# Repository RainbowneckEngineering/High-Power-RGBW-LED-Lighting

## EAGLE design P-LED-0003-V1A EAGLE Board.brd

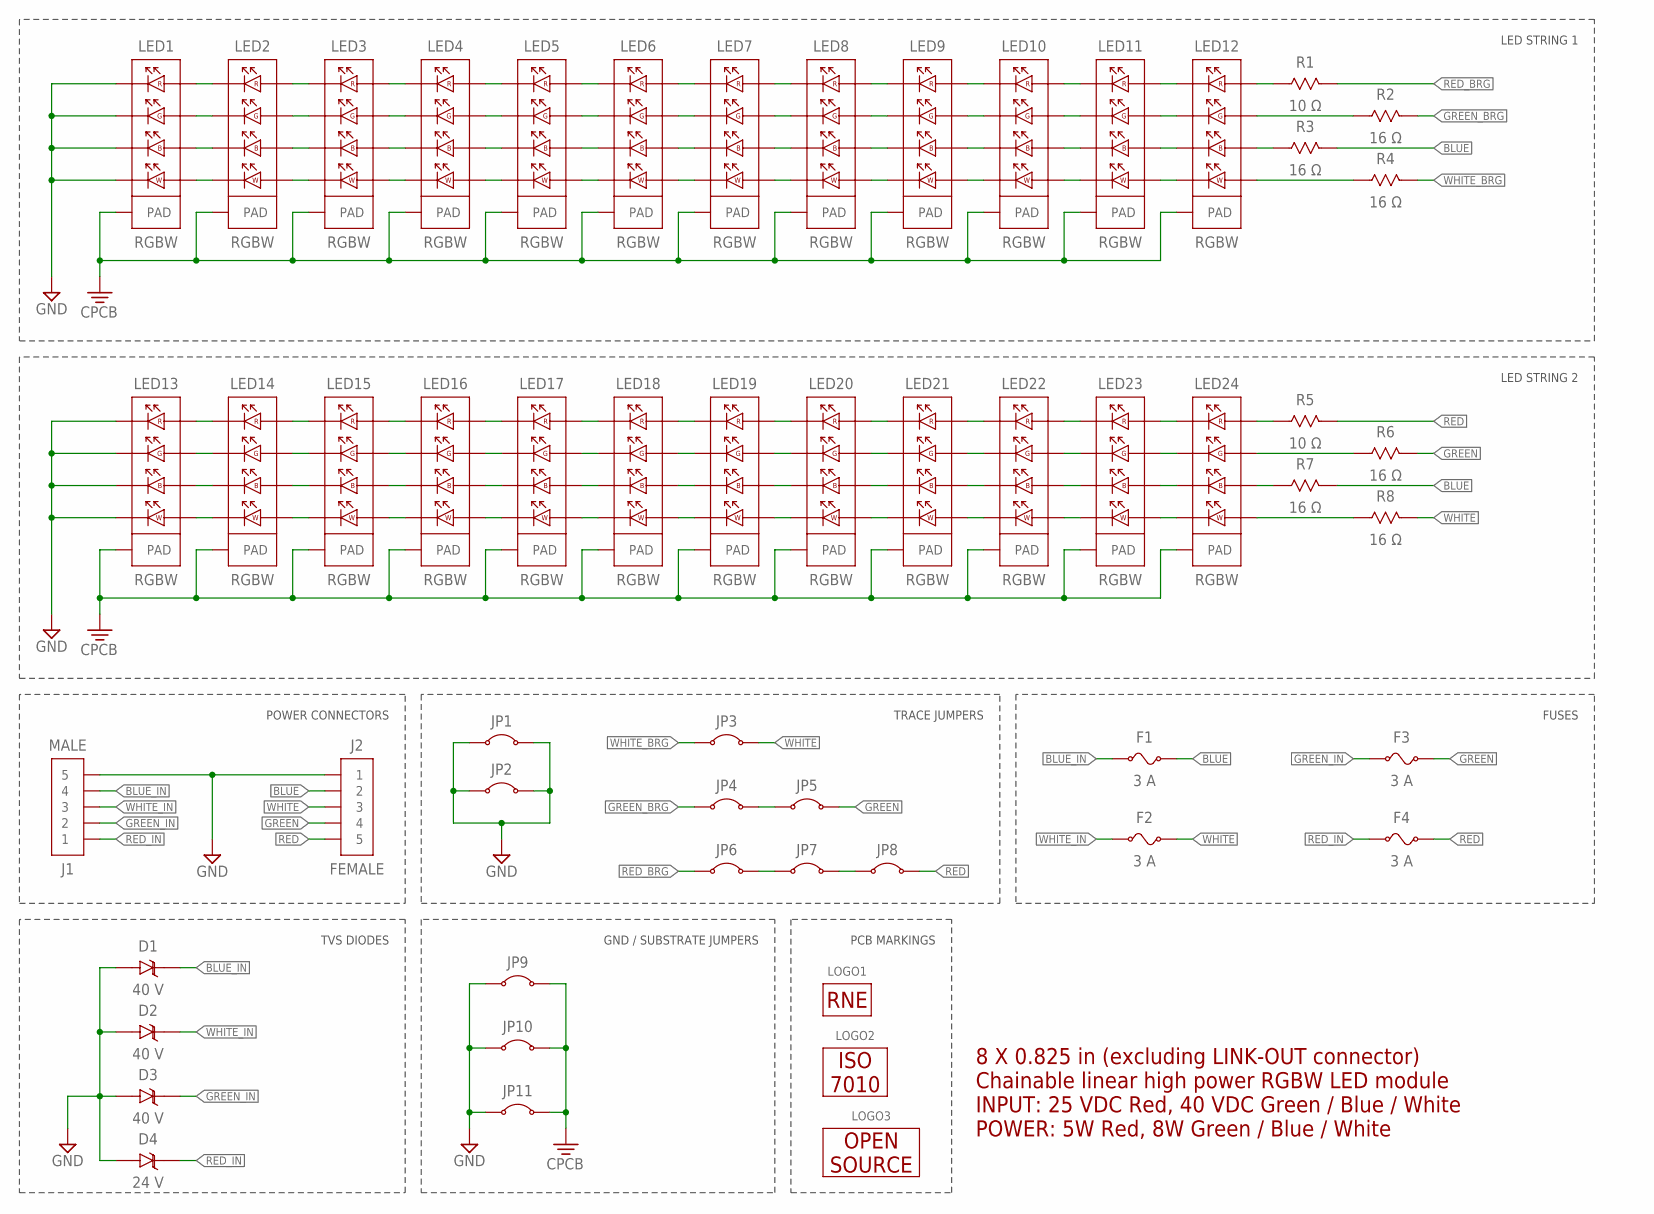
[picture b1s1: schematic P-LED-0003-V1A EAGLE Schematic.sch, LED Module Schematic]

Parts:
D1, D2, D3: 40 V; 0603_POLARIZED
D4: 24 V; 0603_POLARIZED
F1, F2, F3, F4: 3 A; 1206
J1: MALE; 5-PIN_1-ROW_MALE_SMD_HORIZONTAL
J2: FEMALE; 5-PIN_1-ROW_FEMALE_SMD_HORIZONTAL
JP1, JP2, JP3, JP4, JP5, JP6, JP7, JP8: JUMPERSMD_1206; 1206
JP9, JP10, JP11: DCH_JUMPERSMD_0603; 0603
LED1, LED2, LED3, LED4, LED5, LED6, LED7, LED8, LED9, LED10, LED11, LED12, LED13, LED14, LED15, LED16, LED17, LED18, LED19, LED20, LED21, LED22, LED23, LED24: RGBW; IN-P55QSTGRGBW
LOGO1: PROFILE_LOGO_RNE0.375"; RNE_PROFILE-LOGO_375
LOGO2: HOT_SURFACE_ISO0.375"_LABEL; ISO_HOT-SURFACE_375_LABEL
LOGO3: OPEN_SOURCE_OSHWA0.375"_LABEL; OSHWA_OPEN-SOURCE_375_LABEL
R1, R5: 10 Ω; 0603
R2, R3, R4, R6, R7, R8: 16 Ω; 0603

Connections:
B1_RESISTOR: LED12.BLUE_P, R3.1
B2_RESISTOR: LED24.BLUE_P, R7.1
BLUE: F1.2, J2.2, R3.2, R7.2
BLUE_IN: D1.K, F1.1, J1.4
B_12: LED1.BLUE_P, LED2.BLUE_N
B_23: LED2.BLUE_P, LED3.BLUE_N
B_34: LED3.BLUE_P, LED4.BLUE_N
B_45: LED4.BLUE_P, LED5.BLUE_N
B_56: LED5.BLUE_P, LED6.BLUE_N
B_67: LED6.BLUE_P, LED7.BLUE_N
B_78: LED7.BLUE_P, LED8.BLUE_N
B_89: LED8.BLUE_P, LED9.BLUE_N
B_910: LED9.BLUE_P, LED10.BLUE_N
B_1011: LED10.BLUE_P, LED11.BLUE_N
B_1112: LED11.BLUE_P, LED12.BLUE_N
B_1314: LED13.BLUE_P, LED14.BLUE_N
B_1415: LED14.BLUE_P, LED15.BLUE_N
B_1516: LED15.BLUE_P, LED16.BLUE_N
B_1617: LED16.BLUE_P, LED17.BLUE_N
B_1718: LED17.BLUE_P, LED18.BLUE_N
B_1819: LED18.BLUE_P, LED19.BLUE_N
B_1920: LED19.BLUE_P, LED20.BLUE_N
B_2021: LED20.BLUE_P, LED21.BLUE_N
B_2122: LED21.BLUE_P, LED22.BLUE_N
B_2223: LED22.BLUE_P, LED23.BLUE_N
B_2324: LED23.BLUE_P, LED24.BLUE_N
G1_RESISTOR: LED12.GREEN_P, R2.1
G2_RESISTOR: LED24.GREEN_P, R6.1
GREEN: F3.2, J2.4, JP5.2, R6.2
GREEN_BRG: JP4.1, R2.2
GREEN_BRG_2: JP4.2, JP5.1
GREEN_IN: D3.K, F3.1, J1.2
G_12: LED1.GREEN_P, LED2.GREEN_N
G_23: LED2.GREEN_P, LED3.GREEN_N
G_34: LED3.GREEN_P, LED4.GREEN_N
G_45: LED4.GREEN_P, LED5.GREEN_N
G_56: LED5.GREEN_P, LED6.GREEN_N
G_67: LED6.GREEN_P, LED7.GREEN_N
G_78: LED7.GREEN_P, LED8.GREEN_N
G_89: LED8.GREEN_P, LED9.GREEN_N
G_910: LED9.GREEN_P, LED10.GREEN_N
G_1011: LED10.GREEN_P, LED11.GREEN_N
G_1112: LED11.GREEN_P, LED12.GREEN_N
G_1314: LED13.GREEN_P, LED14.GREEN_N
G_1415: LED14.GREEN_P, LED15.GREEN_N
G_1516: LED15.GREEN_P, LED16.GREEN_N
G_1617: LED16.GREEN_P, LED17.GREEN_N
G_1718: LED17.GREEN_P, LED18.GREEN_N
G_1819: LED18.GREEN_P, LED19.GREEN_N
G_1920: LED19.GREEN_P, LED20.GREEN_N
G_2021: LED20.GREEN_P, LED21.GREEN_N
G_2122: LED21.GREEN_P, LED22.GREEN_N
G_2223: LED22.GREEN_P, LED23.GREEN_N
G_2324: LED23.GREEN_P, LED24.GREEN_N
R1_RESISTOR: LED12.RED_P, R1.1
R2_RESISTOR: LED24.RED_P, R5.1
RED: F4.2, J2.5, JP8.2, R5.2
RED_BRG: JP6.1, R1.2
RED_BRG_2: JP6.2, JP7.1
RED_BRG_3: JP7.2, JP8.1
RED_IN: D4.K, F4.1, J1.1
R_12: LED1.RED_P, LED2.RED_N
R_23: LED2.RED_P, LED3.RED_N
R_34: LED3.RED_P, LED4.RED_N
R_45: LED4.RED_P, LED5.RED_N
R_56: LED5.RED_P, LED6.RED_N
R_67: LED6.RED_P, LED7.RED_N
R_78: LED7.RED_P, LED8.RED_N
R_89: LED8.RED_P, LED9.RED_N
R_910: LED9.RED_P, LED10.RED_N
R_1011: LED10.RED_P, LED11.RED_N
R_1112: LED11.RED_P, LED12.RED_N
R_1314: LED13.RED_P, LED14.RED_N
R_1415: LED14.RED_P, LED15.RED_N
R_1516: LED15.RED_P, LED16.RED_N
R_1617: LED16.RED_P, LED17.RED_N
R_1718: LED17.RED_P, LED18.RED_N
R_1819: LED18.RED_P, LED19.RED_N
R_1920: LED19.RED_P, LED20.RED_N
R_2021: LED20.RED_P, LED21.RED_N
R_2122: LED21.RED_P, LED22.RED_N
R_2223: LED22.RED_P, LED23.RED_N
R_2324: LED23.RED_P, LED24.RED_N
W1_RESISTOR: LED12.WHITE_P, R4.1
W2_RESISTOR: LED24.WHITE_P, R8.1
WHITE: F2.2, J2.3, JP3.2, R8.2
WHITE_BRG: JP3.1, R4.2
WHITE_IN: D2.K, F2.1, J1.3
W_12: LED1.WHITE_P, LED2.WHITE_N
W_23: LED2.WHITE_P, LED3.WHITE_N
W_34: LED3.WHITE_P, LED4.WHITE_N
W_45: LED4.WHITE_P, LED5.WHITE_N
W_56: LED5.WHITE_P, LED6.WHITE_N
W_67: LED6.WHITE_P, LED7.WHITE_N
W_78: LED7.WHITE_P, LED8.WHITE_N
W_89: LED8.WHITE_P, LED9.WHITE_N
W_910: LED9.WHITE_P, LED10.WHITE_N
W_1011: LED10.WHITE_P, LED11.WHITE_N
W_1112: LED11.WHITE_P, LED12.WHITE_N
W_1314: LED13.WHITE_P, LED14.WHITE_N
W_1415: LED14.WHITE_P, LED15.WHITE_N
W_1516: LED15.WHITE_P, LED16.WHITE_N
W_1617: LED16.WHITE_P, LED17.WHITE_N
W_1718: LED17.WHITE_P, LED18.WHITE_N
W_1819: LED18.WHITE_P, LED19.WHITE_N
W_1920: LED19.WHITE_P, LED20.WHITE_N
W_2021: LED20.WHITE_P, LED21.WHITE_N
W_2122: LED21.WHITE_P, LED22.WHITE_N
W_2223: LED22.WHITE_P, LED23.WHITE_N
W_2324: LED23.WHITE_P, LED24.WHITE_N

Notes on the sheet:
LED STRING 1
LED STRING 2
POWER CONNECTORS
TRACE JUMPERS
TVS DIODES
GND / SUBSTRATE JUMPERS
FUSES
8 X 0.825 in (excluding LINK-OUT connector) Chainable linear high power RGBW LED module INPUT: 25 VDC Red, 40 VDC Green / Blue / White POWER: 5W Red, 8W Green / Blue / White
PCB MARKINGS

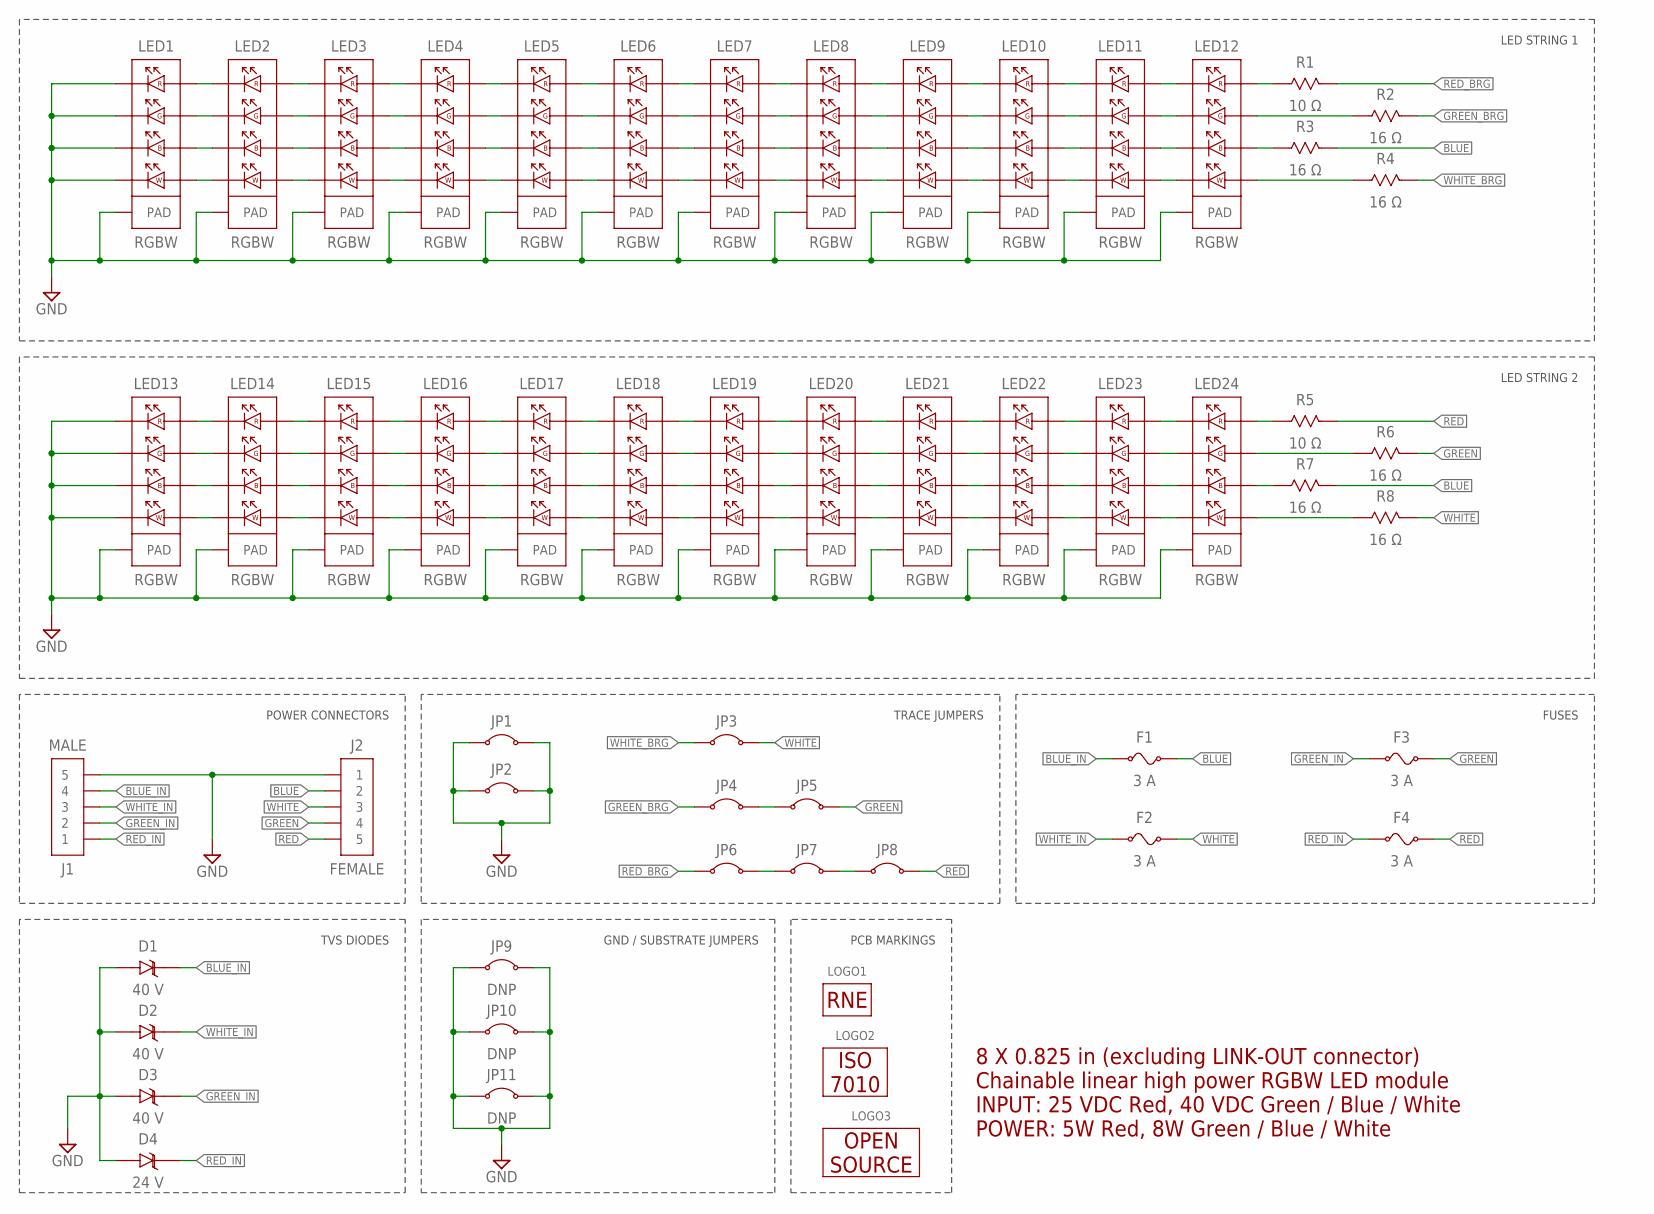
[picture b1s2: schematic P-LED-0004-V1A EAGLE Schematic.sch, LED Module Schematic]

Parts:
D1, D2, D3: 40 V; 0603_POLARIZED
D4: 24 V; 0603_POLARIZED
F1, F2, F3, F4: 3 A; 1206
J1: MALE; 5-PIN_1-ROW_MALE_SMD_HORIZONTAL
J2: FEMALE; 5-PIN_1-ROW_FEMALE_SMD_HORIZONTAL
JP1, JP2, JP3, JP4, JP5, JP6, JP7, JP8: JUMPERSMD_1206; 1206
JP9, JP10, JP11: DNP; 0603
LED1, LED2, LED3, LED4, LED5, LED6, LED7, LED8, LED9, LED10, LED11, LED12, LED13, LED14, LED15, LED16, LED17, LED18, LED19, LED20, LED21, LED22, LED23, LED24: RGBW; IN-P55QSTGRGBW_AIS
LOGO1: PROFILE_LOGO_RNE0.375"; RNE_PROFILE-LOGO_375
LOGO2: HOT_SURFACE_ISO0.375"_LABEL; ISO_HOT-SURFACE_375_LABEL
LOGO3: OPEN_SOURCE_OSHWA0.375"_LABEL; OSHWA_OPEN-SOURCE_375_LABEL
R1, R5: 10 Ω; 0603
R2, R3, R4, R6, R7, R8: 16 Ω; 0603

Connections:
B1_RESISTOR: LED12.BLUE_P, R3.1
B2_RESISTOR: LED24.BLUE_P, R7.1
BLUE: F1.2, J2.2, R3.2, R7.2
BLUE_IN: D1.K, F1.1, J1.4
B_12: LED1.BLUE_P, LED2.BLUE_N
B_23: LED2.BLUE_P, LED3.BLUE_N
B_34: LED3.BLUE_P, LED4.BLUE_N
B_45: LED4.BLUE_P, LED5.BLUE_N
B_56: LED5.BLUE_P, LED6.BLUE_N
B_67: LED6.BLUE_P, LED7.BLUE_N
B_78: LED7.BLUE_P, LED8.BLUE_N
B_89: LED8.BLUE_P, LED9.BLUE_N
B_910: LED9.BLUE_P, LED10.BLUE_N
B_1011: LED10.BLUE_P, LED11.BLUE_N
B_1112: LED11.BLUE_P, LED12.BLUE_N
B_1314: LED13.BLUE_P, LED14.BLUE_N
B_1415: LED14.BLUE_P, LED15.BLUE_N
B_1516: LED15.BLUE_P, LED16.BLUE_N
B_1617: LED16.BLUE_P, LED17.BLUE_N
B_1718: LED17.BLUE_P, LED18.BLUE_N
B_1819: LED18.BLUE_P, LED19.BLUE_N
B_1920: LED19.BLUE_P, LED20.BLUE_N
B_2021: LED20.BLUE_P, LED21.BLUE_N
B_2122: LED21.BLUE_P, LED22.BLUE_N
B_2223: LED22.BLUE_P, LED23.BLUE_N
B_2324: LED23.BLUE_P, LED24.BLUE_N
G1_RESISTOR: LED12.GREEN_P, R2.1
G2_RESISTOR: LED24.GREEN_P, R6.1
GREEN: F3.2, J2.4, JP5.2, R6.2
GREEN_BRG: JP4.1, R2.2
GREEN_BRG_2: JP4.2, JP5.1
GREEN_IN: D3.K, F3.1, J1.2
G_12: LED1.GREEN_P, LED2.GREEN_N
G_23: LED2.GREEN_P, LED3.GREEN_N
G_34: LED3.GREEN_P, LED4.GREEN_N
G_45: LED4.GREEN_P, LED5.GREEN_N
G_56: LED5.GREEN_P, LED6.GREEN_N
G_67: LED6.GREEN_P, LED7.GREEN_N
G_78: LED7.GREEN_P, LED8.GREEN_N
G_89: LED8.GREEN_P, LED9.GREEN_N
G_910: LED9.GREEN_P, LED10.GREEN_N
G_1011: LED10.GREEN_P, LED11.GREEN_N
G_1112: LED11.GREEN_P, LED12.GREEN_N
G_1314: LED13.GREEN_P, LED14.GREEN_N
G_1415: LED14.GREEN_P, LED15.GREEN_N
G_1516: LED15.GREEN_P, LED16.GREEN_N
G_1617: LED16.GREEN_P, LED17.GREEN_N
G_1718: LED17.GREEN_P, LED18.GREEN_N
G_1819: LED18.GREEN_P, LED19.GREEN_N
G_1920: LED19.GREEN_P, LED20.GREEN_N
G_2021: LED20.GREEN_P, LED21.GREEN_N
G_2122: LED21.GREEN_P, LED22.GREEN_N
G_2223: LED22.GREEN_P, LED23.GREEN_N
G_2324: LED23.GREEN_P, LED24.GREEN_N
R1_RESISTOR: LED12.RED_P, R1.1
R2_RESISTOR: LED24.RED_P, R5.1
RED: F4.2, J2.5, JP8.2, R5.2
RED_BRG: JP6.1, R1.2
RED_BRG_2: JP6.2, JP7.1
RED_BRG_3: JP7.2, JP8.1
RED_IN: D4.K, F4.1, J1.1
R_12: LED1.RED_P, LED2.RED_N
R_23: LED2.RED_P, LED3.RED_N
R_34: LED3.RED_P, LED4.RED_N
R_45: LED4.RED_P, LED5.RED_N
R_56: LED5.RED_P, LED6.RED_N
R_67: LED6.RED_P, LED7.RED_N
R_78: LED7.RED_P, LED8.RED_N
R_89: LED8.RED_P, LED9.RED_N
R_910: LED9.RED_P, LED10.RED_N
R_1011: LED10.RED_P, LED11.RED_N
R_1112: LED11.RED_P, LED12.RED_N
R_1314: LED13.RED_P, LED14.RED_N
R_1415: LED14.RED_P, LED15.RED_N
R_1516: LED15.RED_P, LED16.RED_N
R_1617: LED16.RED_P, LED17.RED_N
R_1718: LED17.RED_P, LED18.RED_N
R_1819: LED18.RED_P, LED19.RED_N
R_1920: LED19.RED_P, LED20.RED_N
R_2021: LED20.RED_P, LED21.RED_N
R_2122: LED21.RED_P, LED22.RED_N
R_2223: LED22.RED_P, LED23.RED_N
R_2324: LED23.RED_P, LED24.RED_N
W1_RESISTOR: LED12.WHITE_P, R4.1
W2_RESISTOR: LED24.WHITE_P, R8.1
WHITE: F2.2, J2.3, JP3.2, R8.2
WHITE_BRG: JP3.1, R4.2
WHITE_IN: D2.K, F2.1, J1.3
W_12: LED1.WHITE_P, LED2.WHITE_N
W_23: LED2.WHITE_P, LED3.WHITE_N
W_34: LED3.WHITE_P, LED4.WHITE_N
W_45: LED4.WHITE_P, LED5.WHITE_N
W_56: LED5.WHITE_P, LED6.WHITE_N
W_67: LED6.WHITE_P, LED7.WHITE_N
W_78: LED7.WHITE_P, LED8.WHITE_N
W_89: LED8.WHITE_P, LED9.WHITE_N
W_910: LED9.WHITE_P, LED10.WHITE_N
W_1011: LED10.WHITE_P, LED11.WHITE_N
W_1112: LED11.WHITE_P, LED12.WHITE_N
W_1314: LED13.WHITE_P, LED14.WHITE_N
W_1415: LED14.WHITE_P, LED15.WHITE_N
W_1516: LED15.WHITE_P, LED16.WHITE_N
W_1617: LED16.WHITE_P, LED17.WHITE_N
W_1718: LED17.WHITE_P, LED18.WHITE_N
W_1819: LED18.WHITE_P, LED19.WHITE_N
W_1920: LED19.WHITE_P, LED20.WHITE_N
W_2021: LED20.WHITE_P, LED21.WHITE_N
W_2122: LED21.WHITE_P, LED22.WHITE_N
W_2223: LED22.WHITE_P, LED23.WHITE_N
W_2324: LED23.WHITE_P, LED24.WHITE_N

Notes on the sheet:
LED STRING 1
LED STRING 2
POWER CONNECTORS
TRACE JUMPERS
TVS DIODES
GND / SUBSTRATE JUMPERS
FUSES
8 X 0.825 in (excluding LINK-OUT connector) Chainable linear high power RGBW LED module INPUT: 25 VDC Red, 40 VDC Green / Blue / White POWER: 5W Red, 8W Green / Blue / White
PCB MARKINGS

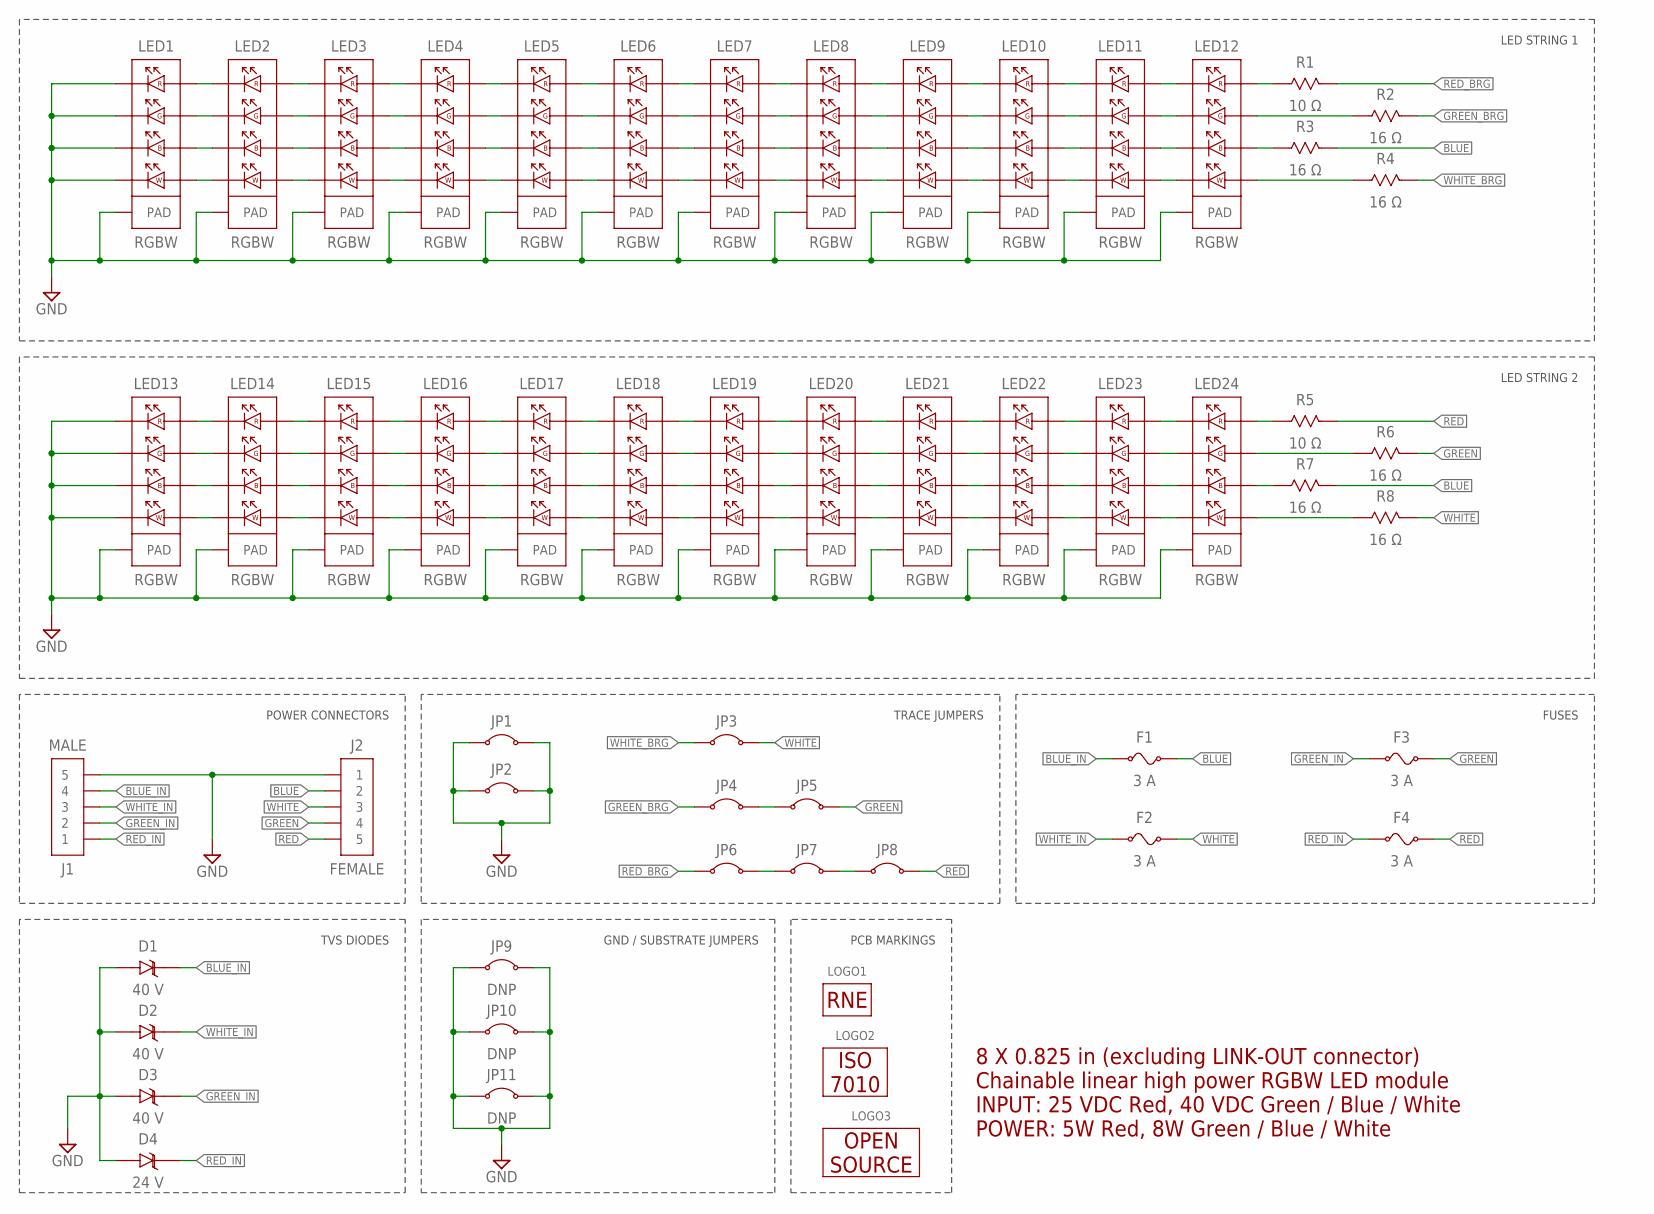
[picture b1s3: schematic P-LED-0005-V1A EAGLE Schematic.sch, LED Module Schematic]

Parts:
D1, D2, D3: 40 V; 0603_POLARIZED
D4: 24 V; 0603_POLARIZED
F1, F2, F3, F4: 3 A; 1206
J1: MALE; 5-PIN_1-ROW_MALE_SMD_HORIZONTAL
J2: FEMALE; 5-PIN_1-ROW_FEMALE_SMD_HORIZONTAL
JP1, JP2, JP3, JP4, JP5, JP6, JP7, JP8: JUMPERSMD_1206; 1206
JP9, JP10, JP11: DNP; 0603
LED1, LED2, LED3, LED4, LED5, LED6, LED7, LED8, LED9, LED10, LED11, LED12, LED13, LED14, LED15, LED16, LED17, LED18, LED19, LED20, LED21, LED22, LED23, LED24: RGBW; IN-P55QSTGRGBW_FR4
LOGO1: PROFILE_LOGO_RNE0.375"; RNE_PROFILE-LOGO_375
LOGO2: HOT_SURFACE_ISO0.375"_LABEL; ISO_HOT-SURFACE_375_LABEL
LOGO3: OPEN_SOURCE_OSHWA0.375"_LABEL; OSHWA_OPEN-SOURCE_375_LABEL
R1, R5: 10 Ω; 0603
R2, R3, R4, R6, R7, R8: 16 Ω; 0603

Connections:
B1_RESISTOR: LED12.BLUE_P, R3.1
B2_RESISTOR: LED24.BLUE_P, R7.1
BLUE: F1.2, J2.2, R3.2, R7.2
BLUE_IN: D1.K, F1.1, J1.4
B_12: LED1.BLUE_P, LED2.BLUE_N
B_23: LED2.BLUE_P, LED3.BLUE_N
B_34: LED3.BLUE_P, LED4.BLUE_N
B_45: LED4.BLUE_P, LED5.BLUE_N
B_56: LED5.BLUE_P, LED6.BLUE_N
B_67: LED6.BLUE_P, LED7.BLUE_N
B_78: LED7.BLUE_P, LED8.BLUE_N
B_89: LED8.BLUE_P, LED9.BLUE_N
B_910: LED9.BLUE_P, LED10.BLUE_N
B_1011: LED10.BLUE_P, LED11.BLUE_N
B_1112: LED11.BLUE_P, LED12.BLUE_N
B_1314: LED13.BLUE_P, LED14.BLUE_N
B_1415: LED14.BLUE_P, LED15.BLUE_N
B_1516: LED15.BLUE_P, LED16.BLUE_N
B_1617: LED16.BLUE_P, LED17.BLUE_N
B_1718: LED17.BLUE_P, LED18.BLUE_N
B_1819: LED18.BLUE_P, LED19.BLUE_N
B_1920: LED19.BLUE_P, LED20.BLUE_N
B_2021: LED20.BLUE_P, LED21.BLUE_N
B_2122: LED21.BLUE_P, LED22.BLUE_N
B_2223: LED22.BLUE_P, LED23.BLUE_N
B_2324: LED23.BLUE_P, LED24.BLUE_N
G1_RESISTOR: LED12.GREEN_P, R2.1
G2_RESISTOR: LED24.GREEN_P, R6.1
GREEN: F3.2, J2.4, JP5.2, R6.2
GREEN_BRG: JP4.1, R2.2
GREEN_BRG_2: JP4.2, JP5.1
GREEN_IN: D3.K, F3.1, J1.2
G_12: LED1.GREEN_P, LED2.GREEN_N
G_23: LED2.GREEN_P, LED3.GREEN_N
G_34: LED3.GREEN_P, LED4.GREEN_N
G_45: LED4.GREEN_P, LED5.GREEN_N
G_56: LED5.GREEN_P, LED6.GREEN_N
G_67: LED6.GREEN_P, LED7.GREEN_N
G_78: LED7.GREEN_P, LED8.GREEN_N
G_89: LED8.GREEN_P, LED9.GREEN_N
G_910: LED9.GREEN_P, LED10.GREEN_N
G_1011: LED10.GREEN_P, LED11.GREEN_N
G_1112: LED11.GREEN_P, LED12.GREEN_N
G_1314: LED13.GREEN_P, LED14.GREEN_N
G_1415: LED14.GREEN_P, LED15.GREEN_N
G_1516: LED15.GREEN_P, LED16.GREEN_N
G_1617: LED16.GREEN_P, LED17.GREEN_N
G_1718: LED17.GREEN_P, LED18.GREEN_N
G_1819: LED18.GREEN_P, LED19.GREEN_N
G_1920: LED19.GREEN_P, LED20.GREEN_N
G_2021: LED20.GREEN_P, LED21.GREEN_N
G_2122: LED21.GREEN_P, LED22.GREEN_N
G_2223: LED22.GREEN_P, LED23.GREEN_N
G_2324: LED23.GREEN_P, LED24.GREEN_N
R1_RESISTOR: LED12.RED_P, R1.1
R2_RESISTOR: LED24.RED_P, R5.1
RED: F4.2, J2.5, JP8.2, R5.2
RED_BRG: JP6.1, R1.2
RED_BRG_2: JP6.2, JP7.1
RED_BRG_3: JP7.2, JP8.1
RED_IN: D4.K, F4.1, J1.1
R_12: LED1.RED_P, LED2.RED_N
R_23: LED2.RED_P, LED3.RED_N
R_34: LED3.RED_P, LED4.RED_N
R_45: LED4.RED_P, LED5.RED_N
R_56: LED5.RED_P, LED6.RED_N
R_67: LED6.RED_P, LED7.RED_N
R_78: LED7.RED_P, LED8.RED_N
R_89: LED8.RED_P, LED9.RED_N
R_910: LED9.RED_P, LED10.RED_N
R_1011: LED10.RED_P, LED11.RED_N
R_1112: LED11.RED_P, LED12.RED_N
R_1314: LED13.RED_P, LED14.RED_N
R_1415: LED14.RED_P, LED15.RED_N
R_1516: LED15.RED_P, LED16.RED_N
R_1617: LED16.RED_P, LED17.RED_N
R_1718: LED17.RED_P, LED18.RED_N
R_1819: LED18.RED_P, LED19.RED_N
R_1920: LED19.RED_P, LED20.RED_N
R_2021: LED20.RED_P, LED21.RED_N
R_2122: LED21.RED_P, LED22.RED_N
R_2223: LED22.RED_P, LED23.RED_N
R_2324: LED23.RED_P, LED24.RED_N
W1_RESISTOR: LED12.WHITE_P, R4.1
W2_RESISTOR: LED24.WHITE_P, R8.1
WHITE: F2.2, J2.3, JP3.2, R8.2
WHITE_BRG: JP3.1, R4.2
WHITE_IN: D2.K, F2.1, J1.3
W_12: LED1.WHITE_P, LED2.WHITE_N
W_23: LED2.WHITE_P, LED3.WHITE_N
W_34: LED3.WHITE_P, LED4.WHITE_N
W_45: LED4.WHITE_P, LED5.WHITE_N
W_56: LED5.WHITE_P, LED6.WHITE_N
W_67: LED6.WHITE_P, LED7.WHITE_N
W_78: LED7.WHITE_P, LED8.WHITE_N
W_89: LED8.WHITE_P, LED9.WHITE_N
W_910: LED9.WHITE_P, LED10.WHITE_N
W_1011: LED10.WHITE_P, LED11.WHITE_N
W_1112: LED11.WHITE_P, LED12.WHITE_N
W_1314: LED13.WHITE_P, LED14.WHITE_N
W_1415: LED14.WHITE_P, LED15.WHITE_N
W_1516: LED15.WHITE_P, LED16.WHITE_N
W_1617: LED16.WHITE_P, LED17.WHITE_N
W_1718: LED17.WHITE_P, LED18.WHITE_N
W_1819: LED18.WHITE_P, LED19.WHITE_N
W_1920: LED19.WHITE_P, LED20.WHITE_N
W_2021: LED20.WHITE_P, LED21.WHITE_N
W_2122: LED21.WHITE_P, LED22.WHITE_N
W_2223: LED22.WHITE_P, LED23.WHITE_N
W_2324: LED23.WHITE_P, LED24.WHITE_N

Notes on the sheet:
LED STRING 1
LED STRING 2
POWER CONNECTORS
TRACE JUMPERS
TVS DIODES
GND / SUBSTRATE JUMPERS
FUSES
8 X 0.825 in (excluding LINK-OUT connector) Chainable linear high power RGBW LED module INPUT: 25 VDC Red, 40 VDC Green / Blue / White POWER: 5W Red, 8W Green / Blue / White
PCB MARKINGS

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
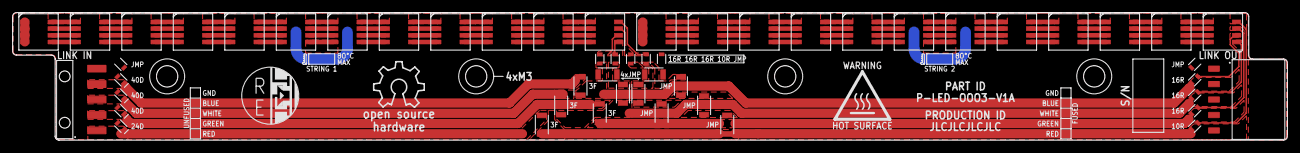
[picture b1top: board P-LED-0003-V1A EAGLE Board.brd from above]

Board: 2 copper layers, 209.6 x 21.0 mm, 56 parts (0 on the bottom side), 112 nets.
